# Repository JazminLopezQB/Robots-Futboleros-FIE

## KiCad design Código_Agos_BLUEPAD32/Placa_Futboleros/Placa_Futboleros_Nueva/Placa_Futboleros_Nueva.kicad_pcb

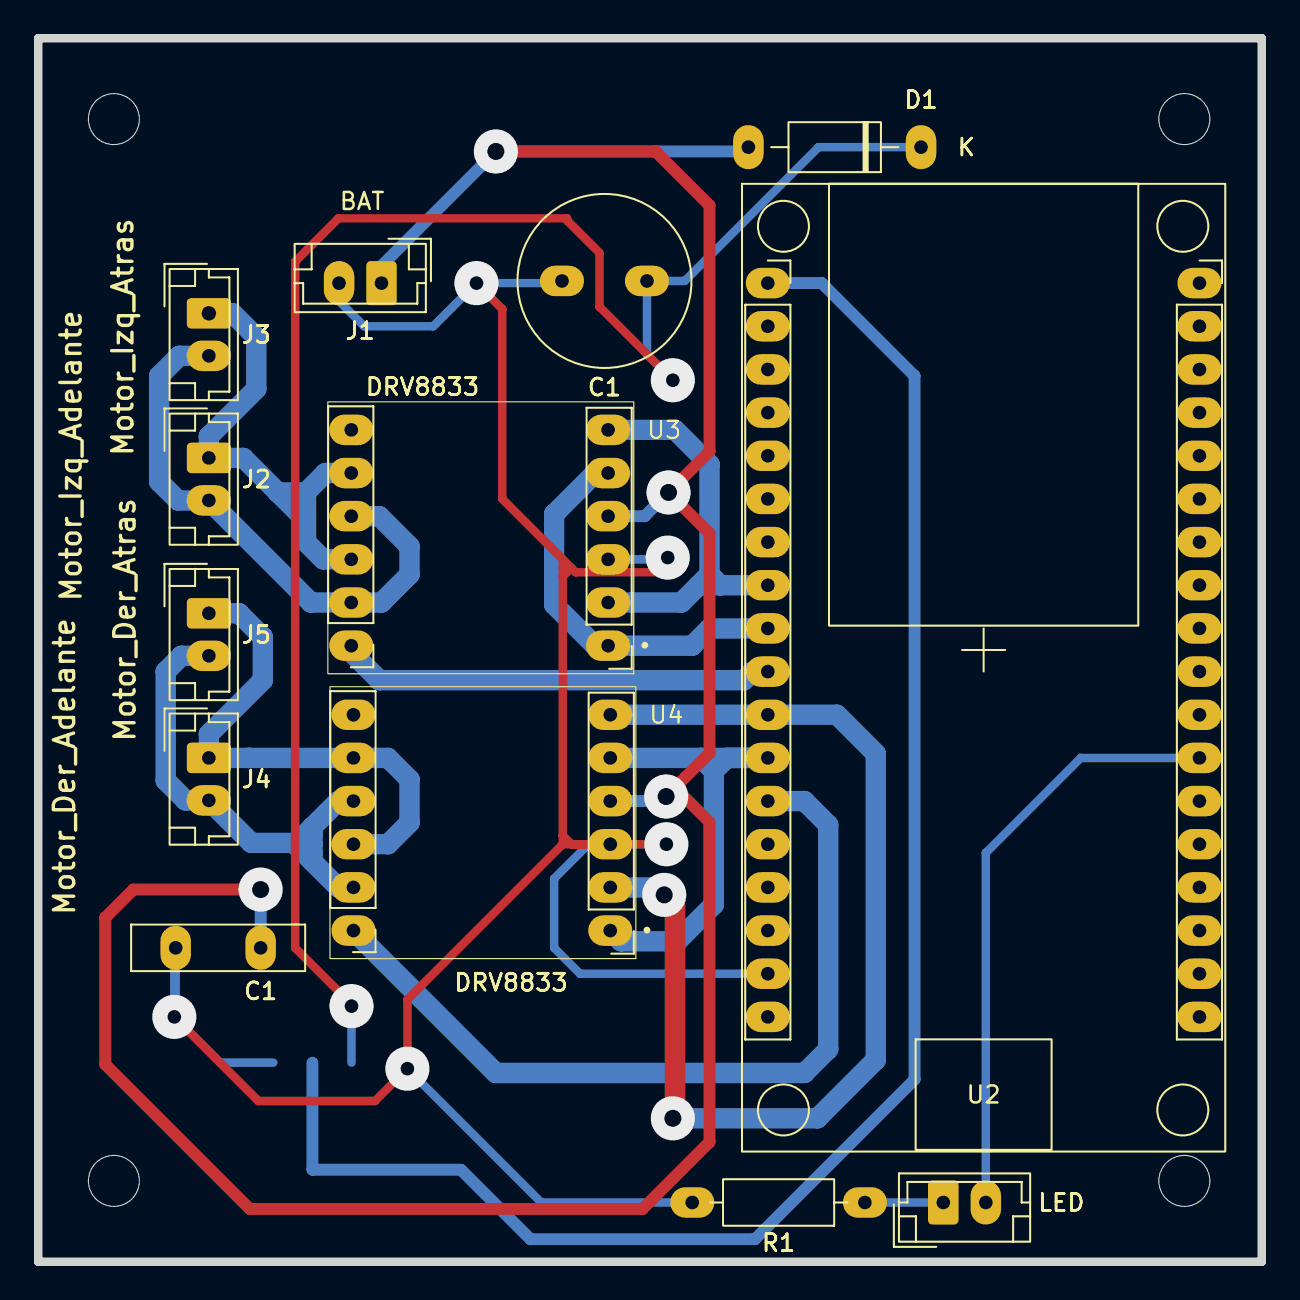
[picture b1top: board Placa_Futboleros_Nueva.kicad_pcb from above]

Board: 2 copper layers, 72.0 x 72.0 mm, 18 parts (1 on the bottom side), 16 nets.

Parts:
C1: 470uF; C_Radial_D10.0mm_H12.5mm_P5.00mm
C1#2: 100n; C_Disc_D10.0mm_W2.5mm_P5.00mm
D1: 1N5819; D_DO-41_SOD81_P10.16mm_Horizontal
H1, H2, H3, H4: MountingHole; MountingHole_3mm
J1: BAT; JST_EH_B2B-EH-A_1x02_P2.50mm_Vertical
J2: Motor_Izq_Adelante; JST_EH_B2B-EH-A_1x02_P2.50mm_Vertical
J3: Motor_Izq_Atras; JST_EH_B2B-EH-A_1x02_P2.50mm_Vertical
J4: Motor_Der_Adelante; JST_EH_B2B-EH-A_1x02_P2.50mm_Vertical
J5: Motor_Der_Atras; JST_EH_B2B-EH-A_1x02_P2.50mm_Vertical
LED: LED_RED; JST_EH_B2B-EH-A_1x02_P2.50mm_Vertical
R1: 220; R_Axial_DIN0207_L6.3mm_D2.5mm_P10.16mm_Horizontal
U1: AMS1117; SOT-223-3_TabPin2
U2: esp32_36_pins-custom_library; PinSocket_1x18_P2.54mm_Vertical
U3, U4: DRV8833

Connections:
+5V: U1.2 (VO), U2.1 (EN_RST)
GND: C1.2, C1#2.2, J1.2, R1.2, U1.1 (ADJ), U2.17 (GND), U3.3 (GND), U4.3 (GND)
IN_M1A: U2.9 (GPIO26), U3.1 (IN4), U3.5 (IN2)
IN_M1B: U2.8 (GPIO25), U3.2 (IN3), U3.6 (IN1)
IN_M2A: U2.12 (GPIO12), U4.1 (IN4), U4.5 (IN2)
IN_M2B: U2.11 (GPIO14), U4.2 (IN3), U4.6 (IN1)
LED_Encendido: LED.2 (A), U2.25 (GPI02)
unnamed: C1.1, D1.1 (K), U1.3 (VI)
unnamed: LED.1 (K), R1.1
unnamed: J2.1, J3.1, U3.8 (OUT4), U3.10 (OUT2)
unnamed: J2.2, J3.2, U3.9 (OUT3), U3.11 (OUT1)
unnamed: J4.1, J5.1, U4.8 (OUT4), U4.10 (OUT2)
unnamed: J4.2, J5.2, U4.9 (OUT3), U4.11 (OUT1)
SLEEP_M1: U2.10 (GPIO27), U3.12 (SLEEP)
SLEEP_M2: U2.13 (GPIO13), U4.12 (SLEEP)
VCC: C1#2.1, D1.2 (A), J1.1, U3.4 (VCC), U4.4 (VCC)
